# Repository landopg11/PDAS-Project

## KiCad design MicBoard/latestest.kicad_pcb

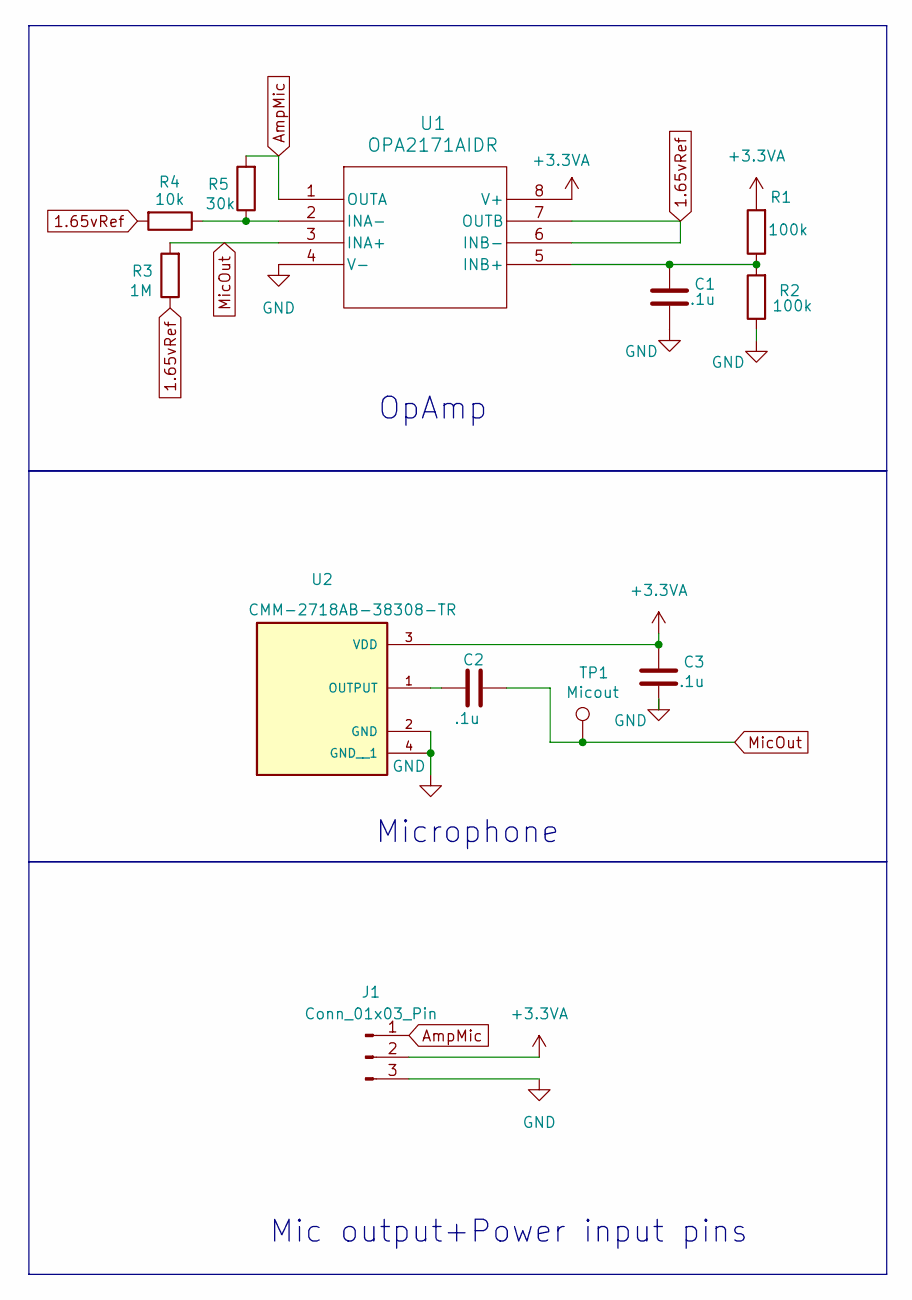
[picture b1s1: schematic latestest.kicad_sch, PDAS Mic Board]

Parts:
C1, C2, C3: .1u; C_0603_1608Metric_Pad1.08x0.95mm_HandSolder
J1: Conn_01x03_Pin; PinHeader_1x03_P2.54mm_Vertical
R1, R2: 100k; R_0603_1608Metric_Pad0.98x0.95mm_HandSolder
R3: 1M; R_0603_1608Metric_Pad0.98x0.95mm_HandSolder
R4: 10k; R_0603_1608Metric_Pad0.98x0.95mm_HandSolder
R5: 30k; R_0603_1608Metric_Pad0.98x0.95mm_HandSolder
TP1: Micout; TestPoint_THTPad_D2.5mm_Drill1.2mm
U1: OPA2171AIDR; D8
U2: CMM-2718AB-38308-TR; XDCR_CMM-2718AB-38308-TR

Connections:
1.65vRef: R3.1, R4.2, U1.6 (INB-), U1.7 (OUTB)
+3.3VA: C3.1, J1.2, R1.2, U1.8 (V+), U2.3 (VDD)
AmpMic: J1.1, R5.2, U1.1 (OUTA)
GND: C1.2, C3.2, J1.3, R2.1, U1.4 (V-), U2.2 (GND), U2.4 (GND__1)
MicOut: C2.2, R3.2, TP1.1, U1.3 (INA+)
unnamed: R4.1, R5.1, U1.2 (INA-)
unnamed: C1.1, R1.1, R2.2, U1.5 (INB+)
unnamed: C2.1, U2.1 (OUTPUT)

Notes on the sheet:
OpAmp
Mic output+Power input pins
Microphone

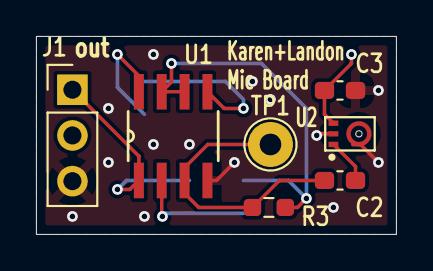
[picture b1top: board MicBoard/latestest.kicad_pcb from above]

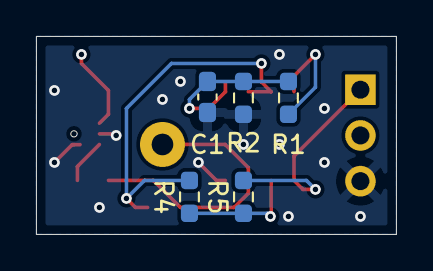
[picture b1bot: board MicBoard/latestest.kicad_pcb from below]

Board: 4 copper layers, 20.0 x 11.0 mm, 12 parts (5 on the bottom side), 8 nets.

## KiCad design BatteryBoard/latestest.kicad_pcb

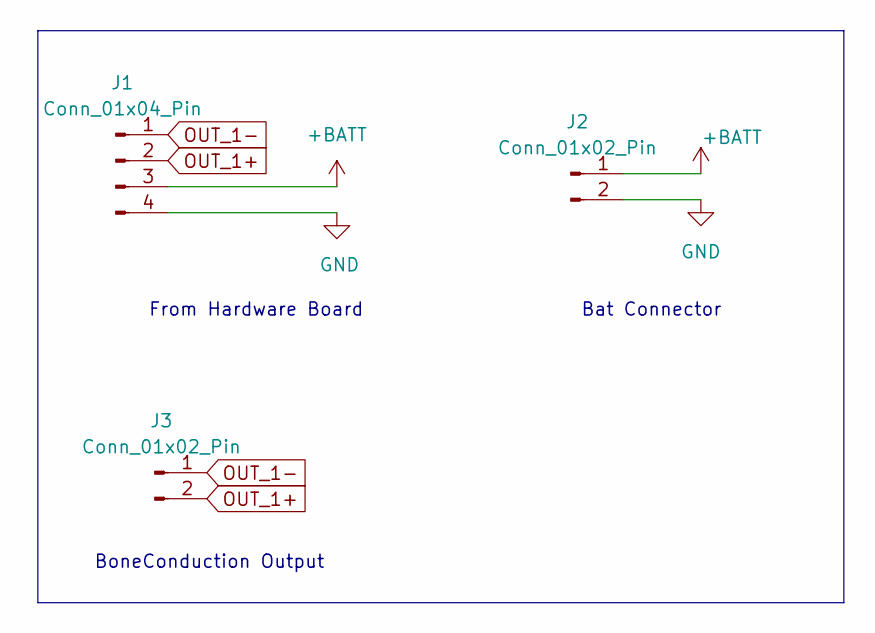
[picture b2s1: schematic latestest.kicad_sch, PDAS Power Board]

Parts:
J1: Conn_01x04_Pin; PinHeader_1x04_P2.54mm_Vertical
J2: Conn_01x02_Pin; Molex_PicoBlade_53047-0210_1x02_P1.25mm_Vertical
J3: Conn_01x02_Pin; PinHeader_1x02_P2.54mm_Vertical

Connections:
+BATT: J1.3, J2.1
GND: J1.4, J2.2
OUT_1+: J1.2, J3.2
OUT_1-: J1.1, J3.1

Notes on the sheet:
BoneConduction Output
From Hardware Board
Bat Connector

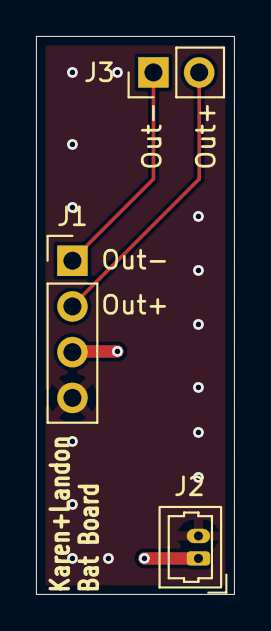
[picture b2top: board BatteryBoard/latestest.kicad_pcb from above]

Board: 4 copper layers, 11.0 x 31.0 mm, 3 parts (0 on the bottom side), 4 nets.
